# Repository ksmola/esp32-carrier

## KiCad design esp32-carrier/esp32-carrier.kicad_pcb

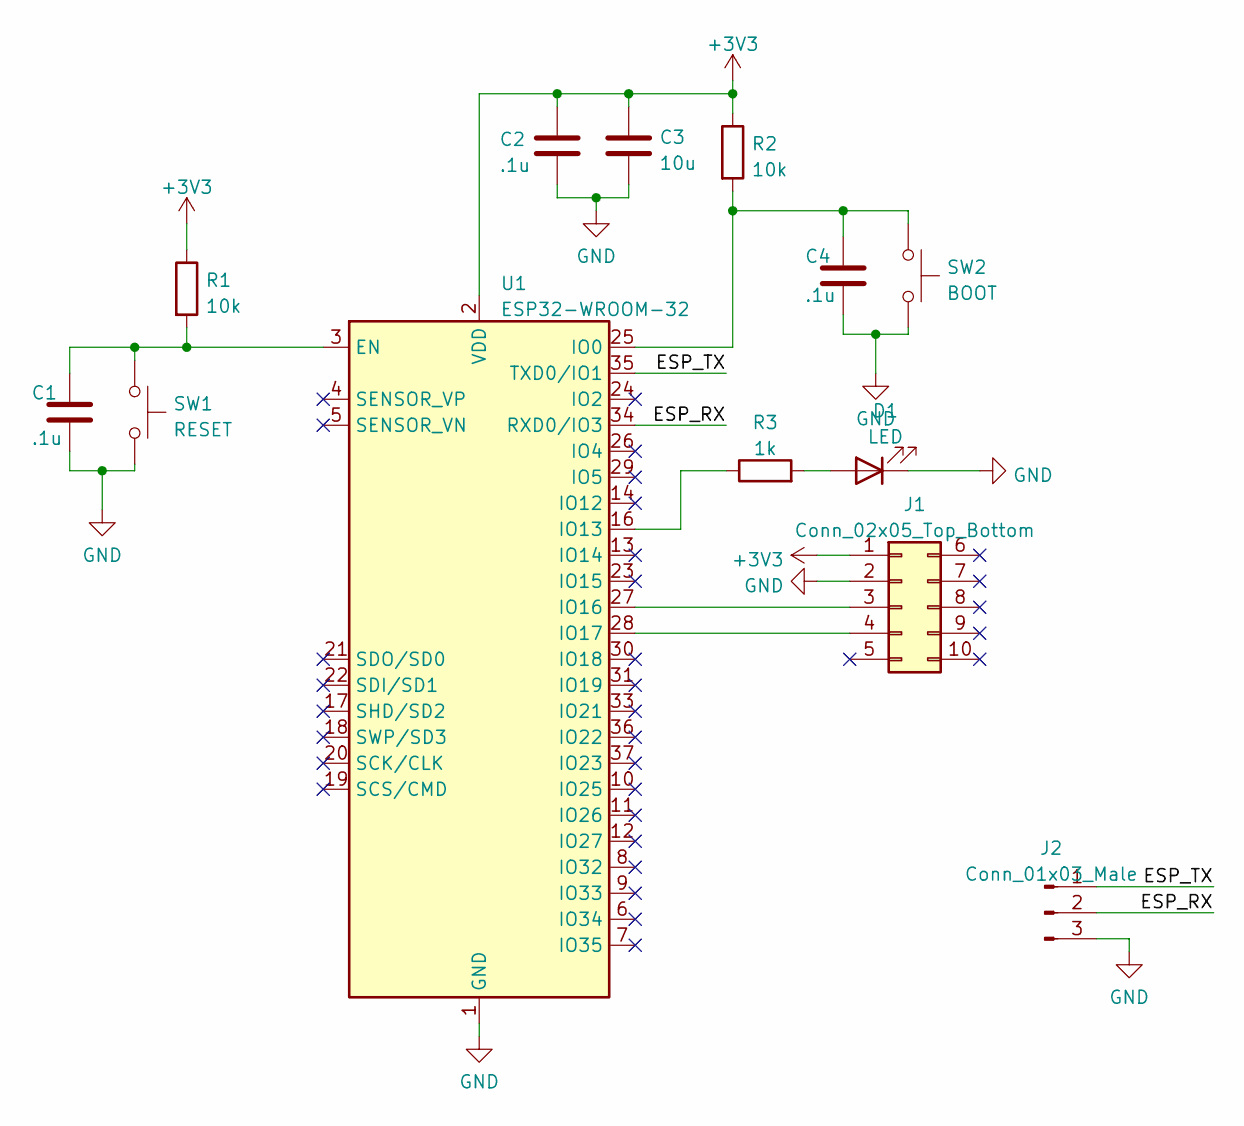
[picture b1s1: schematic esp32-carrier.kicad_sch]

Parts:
C1, C2, C4: .1u; C_0402_1005Metric
C3: 10u; C_0603_1608Metric
D1: LED; LED_0603_1608Metric; LCSC C72041
J1: Conn_02x05_Top_Bottom; PinSocket_2x05_P2.54mm_Vertical
J2: Conn_01x03_Male; PinSocket_1x03_P2.54mm_Vertical
R1, R2: 10k; R_0402_1005Metric; LCSC C25744
R3: 1k; R_0402_1005Metric; LCSC C11702
SW1: RESET; SW_SPST_EVQQ2
SW2: BOOT; SW_SPST_EVQQ2
U1: ESP32-WROOM-32

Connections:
+3V3: C2.1, C3.1, J1.1, R1.1, R2.1, U1.2 (VDD)
/ESP_RX: J2.2, U1.34 (RXD0/IO3)
/ESP_TX: J2.1, U1.35 (TXD0/IO1)
GND: C1.2, C2.2, C3.2, C4.2, D1.1 (K), J1.2, J2.3, SW1.2, SW2.2, U1.1 (GND), U1.15 (GND), U1.38 (GND), U1.39 (GND)
unnamed: C1.1, R1.2, SW1.1, U1.3 (EN)
unnamed: C4.1, R2.2, SW2.1, U1.25 (IO0)
unnamed: D1.2 (A), R3.2
unnamed: J1.3, U1.27 (IO16)
unnamed: J1.4, U1.28 (IO17)
unnamed: R3.1, U1.16 (IO13)

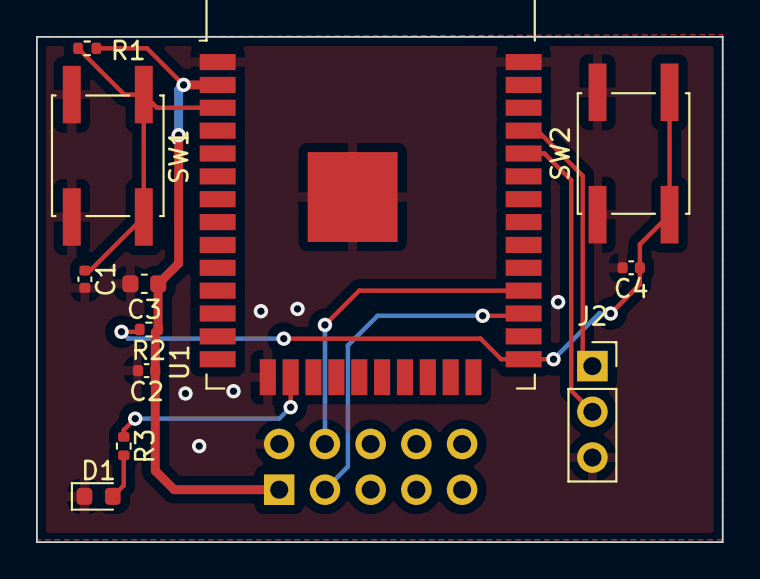
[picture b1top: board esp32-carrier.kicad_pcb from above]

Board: 2 copper layers, 38.1 x 28.1 mm, 13 parts (1 on the bottom side), 10 nets.

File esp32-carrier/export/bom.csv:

Designator,Footprint,Quantity,Value,LCSC Part #
C2,C_0402_1005Metric,1,.1u,
J2,PinSocket_1x03_P2.54mm_Vertical,1,Conn_01x03_Male,
SW1,SW_SPST_EVQQ2,1,RESET,
C4,C_0402_1005Metric,1,.1u,
R2,R_0402_1005Metric,1,10k,C25744
D1,LED_0603_1608Metric,1,LED,C72041
C3,C_0603_1608Metric,1,10u,
SW2,SW_SPST_EVQQ2,1,BOOT,
U1,ESP32-WROOM-32,1,ESP32-WROOM-32,
C1,C_0402_1005Metric,1,.1u,
R3,R_0402_1005Metric,1,1k,C11702
R1,R_0402_1005Metric,1,10k,C25744
J1,PinSocket_2x05_P2.54mm_Vertical,1,Conn_02x05_Top_Bottom,
